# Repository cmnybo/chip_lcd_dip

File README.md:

# C.H.I.P. LCD Adapter & SPI Multiplexer

This DIP is compatible with the following touch screen LCD panels (resistive touch version only):

1. [4.3" 480x272](http://www.buydisplay.com/default/tft-4-3-inch-lcd-module-touchscreen-display-for-mp4-gps-480x272)
2. [5" 800x480](http://www.buydisplay.com/default/5-tft-lcd-display-module-wvga-800x480-high-resolution-for-mp4-gps)
3. [7" 800x480](http://www.buydisplay.com/default/7-tft-lcd-touch-screen-display-module-800x480-for-mp4-gps-tablet-pc)

## Features

* PWM controlled backlight driver
* 8 channel chip select multiplexer for SPI
* 34 pin gpio header that can be connected with old floppy drive cables
* Pin headers for the UART and power switch
* 5.5x2.5mm barrel jack to supply power (5V 2.5A)

The original design files for this board were created in [KiCAD](http://kicad-pcb.org/). <br/>
There are PDF copies of the schematic, PCB layout, and bill of materials in the "pdf" directory.<br/>
The "gerber" directory contains all of the files needed to have some boards made.<br/>
The device tree overlay, kernel patch, and EEPROM image are in the "source" directory.

## License
**This project is open source hardware.**

All files are licensed under a [Creative Commons Attribution-ShareAlike](https://creativecommons.org/licenses/by-sa/3.0) license.

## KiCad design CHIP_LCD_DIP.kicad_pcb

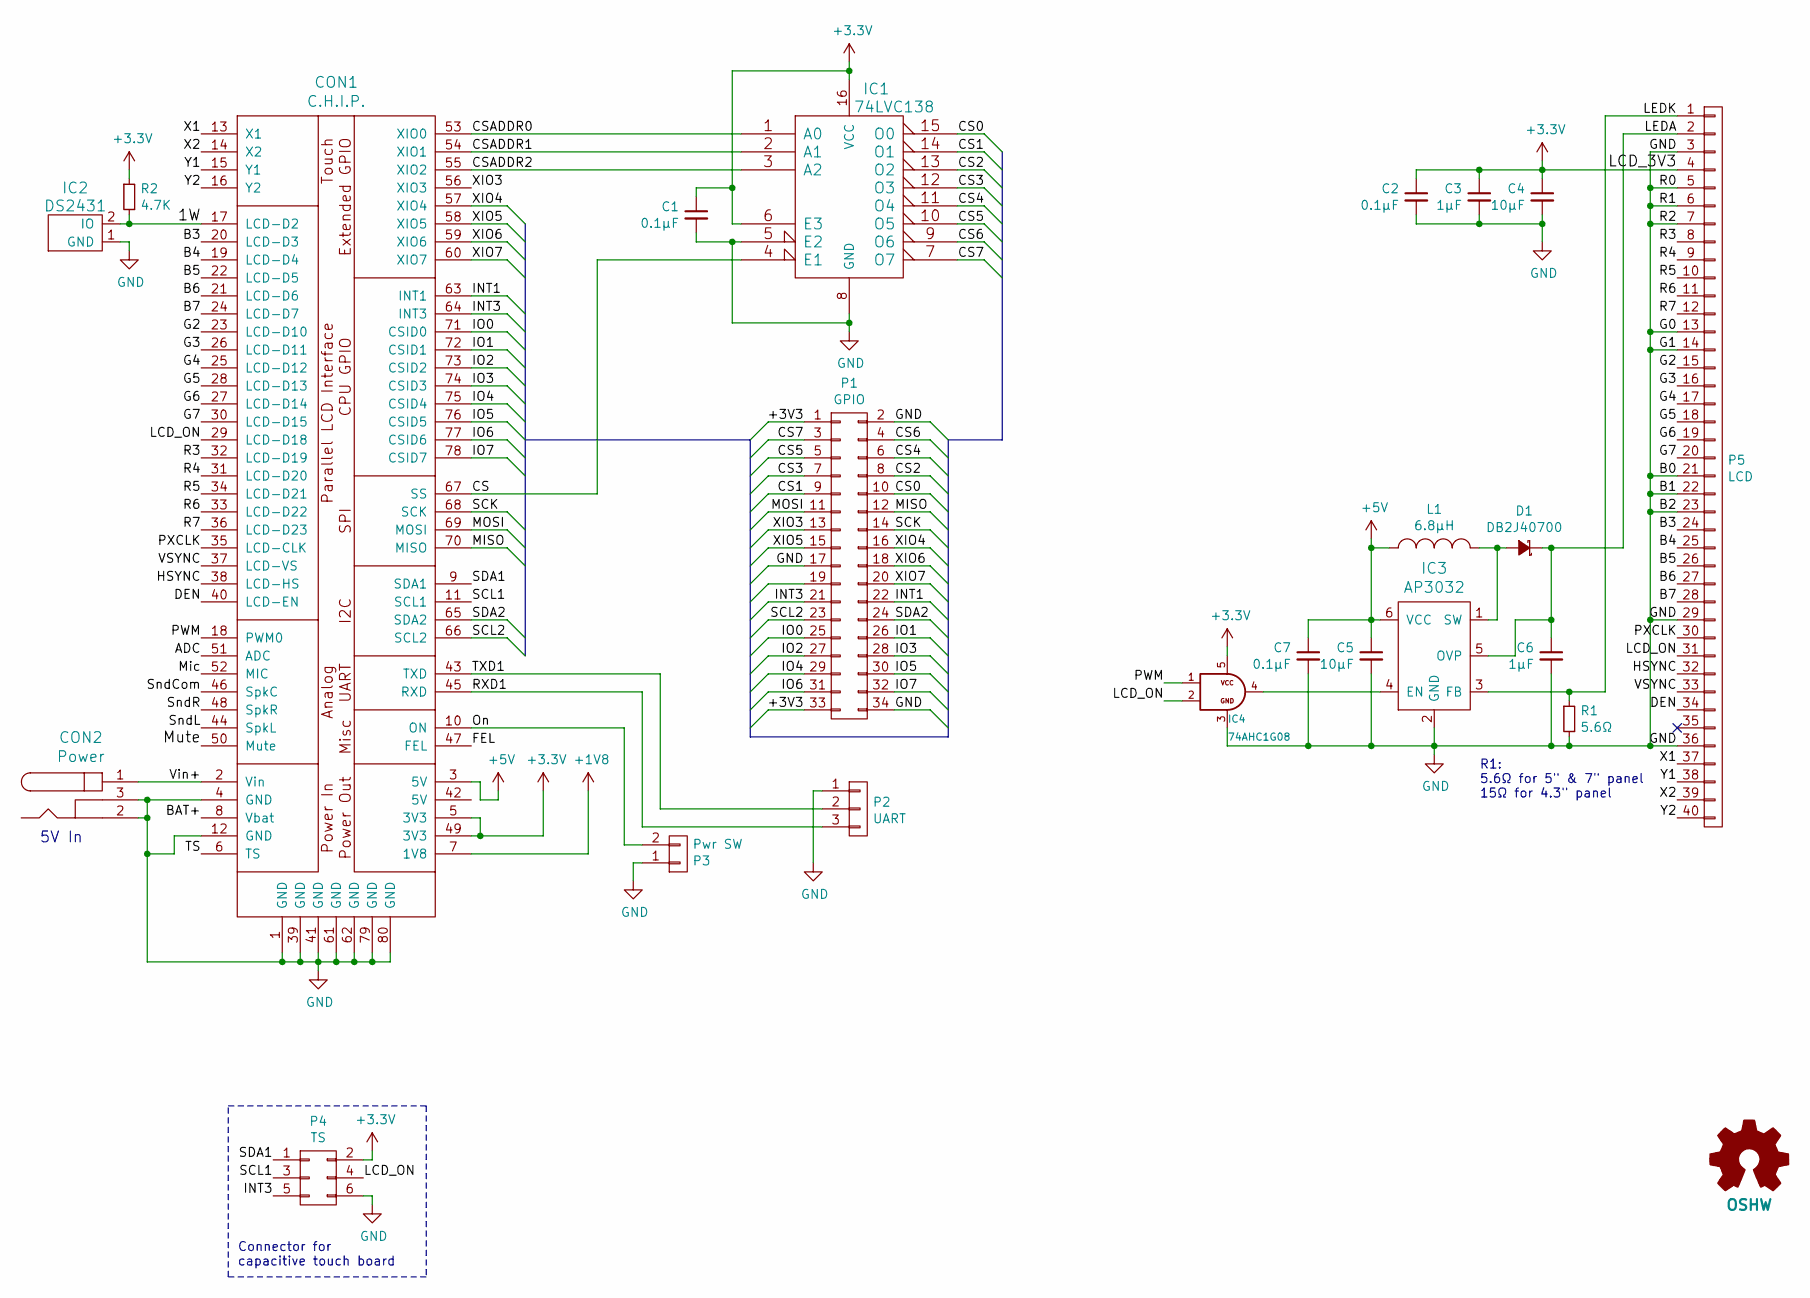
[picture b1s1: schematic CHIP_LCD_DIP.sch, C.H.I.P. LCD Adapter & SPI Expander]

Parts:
C1, C2, C7: 0.1µF; C_0603; Voltage 25V; Tolerance 10%; DigiKey 1276-1006-1-ND
C3: 1µF; C_0603; Voltage 16V; Tolerance 20%; DigiKey 1276-6524-1-ND
C4: 10µF; C_0805; Voltage 6.3V; Tolerance 10%; DigiKey 1276-6457-1-ND
C5: 10µF; C_0603; Voltage 6.3V; Tolerance 10%; DigiKey 490-12538-1-ND
C6: 1µF; C_0603; Voltage 50V; Tolerance 10%; DigiKey 1276-1860-1-ND
CON1: C.H.I.P.; CHIP_DIP
CON2: Power; BARREL_JACK; DigiKey CP-002B-ND
D1: DB2J40700; SOD-323; Voltage 40V; DigiKey DB2J40700LCT-ND
IC1: 74LVC138; SOIC-16_3.9x9.9mm_Pitch1.27mm; DigiKey 568-1577-5-ND
IC2: DS2431; TO-92_Inline_Narrow_Oval; DigiKey DS2431+-ND
IC3: AP3032; SOT-23-6; DigiKey AP3032KTR-G1DICT-ND
IC4: 74AHC1G08; SC-70-5; DigiKey 568-2501-1-ND
L1: 6.8µH; TDK_VLS-E-CA; Tolerance 20%; DigiKey 445-174144-1-ND
LOGO1: OSHW
P1: GPIO; vasch_strip_17x2; DigiKey ED10528-ND
P2: UART; Pin_Header_Straight_1x03; DigiKey 952-2245-ND
P3: Pwr SW; Pin_Header_Straight_1x02; DigiKey 952-2244-ND
P4: TS; 02x03_Header_0.05
P5: LCD; TE_40_PIN_LCD_Connector; DigiKey 609-1195-1-ND
R1: 5.6Ω; C_0603; Tolerance 5%; Voltage 75V; DigiKey 311-5.6GRCT-ND
R2: 4.7K; C_0603; Tolerance 5%; Voltage 75V; DigiKey 311-4.7KGRCT-ND

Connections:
+1V8: CON1.7 (1V8)
+5V: C5.1, C7.1, CON1.3 (5V), IC3.6 (VCC), L1.1
/1W: CON1.17 (LCD-D2), IC2.2 (IO), R2.2
/ADC: CON1.51 (ADC)
/B3: CON1.20 (LCD-D3), P5.24
/B4: CON1.19 (LCD-D4), P5.25
/B5: CON1.22 (LCD-D5), P5.26
/B6: CON1.21 (LCD-D6), P5.27
/B7: CON1.24 (LCD-D7), P5.28
/BAT+: CON1.8 (Vbat)
/CS: CON1.67 (SS), IC1.4 (E1)
/CS0: IC1.15 (O0), P1.10
/CS1: IC1.14 (O1), P1.9
/CS2: IC1.13 (O2), P1.8
/CS3: IC1.12 (O3), P1.7
/CS4: IC1.11 (O4), P1.6
/CS5: IC1.10 (O5), P1.5
/CS6: IC1.9 (O6), P1.4
/CS7: IC1.7 (O7), P1.3
/CSADDR0: CON1.53 (XIO0), IC1.1 (A0)
/CSADDR1: CON1.54 (XIO1), IC1.2 (A1)
/CSADDR2: CON1.55 (XIO2), IC1.3 (A2)
/DEN: CON1.40 (LCD-EN), P5.34
/FEL: CON1.47 (FEL)
/G2: CON1.23 (LCD-D10), P5.15
/G3: CON1.26 (LCD-D11), P5.16
/G4: CON1.25 (LCD-D12), P5.17
/G5: CON1.28 (LCD-D13), P5.18
/G6: CON1.27 (LCD-D14), P5.19
/G7: CON1.30 (LCD-D15), P5.20
/HSYNC: CON1.38 (LCD-HS), P5.32
/INT1: CON1.63 (INT1), P1.22
/INT3: CON1.64 (INT3), P1.21, P4.5
/IO0: CON1.71 (CSID0), P1.25
/IO1: CON1.72 (CSID1), P1.26
/IO2: CON1.73 (CSID2), P1.27
/IO3: CON1.74 (CSID3), P1.28
/IO4: CON1.75 (CSID4), P1.29
/IO5: CON1.76 (CSID5), P1.30
/IO6: CON1.77 (CSID6), P1.31
/IO7: CON1.78 (CSID7), P1.32
/LCD_ON: CON1.29 (LCD-D18), IC4.2, P4.4, P5.31
/LEDA: C6.1, D1.1 (K), IC3.5 (OVP), P5.2
/LEDK: IC3.3 (FB), P5.1, R1.1
/MISO: CON1.70 (MISO), P1.12
/MOSI: CON1.69 (MOSI), P1.11
/Mic: CON1.52 (MIC)
/Mute: CON1.50 (Mute)
/On: CON1.10 (ON), P3.2
/PWM: CON1.18 (PWM0), IC4.1
/PXCLK: CON1.35 (LCD-CLK), P5.30
/R3: CON1.32 (LCD-D19), P5.8
/R4: CON1.31 (LCD-D20), P5.9
/R5: CON1.34 (LCD-D21), P5.10
/R6: CON1.33 (LCD-D22), P5.11
/R7: CON1.36 (LCD-D23), P5.12
/RXD1: CON1.45 (RXD), P2.3
/SCK: CON1.68 (SCK), P1.14
/SCL1: CON1.11 (SCL1), P4.3
/SCL2: CON1.66 (SCL2), P1.23
/SDA1: CON1.9 (SDA1), P4.1
/SDA2: CON1.65 (SDA2), P1.24
/SndCom: CON1.46 (SpkC)
/SndL: CON1.44 (SpkL)
/SndR: CON1.48 (SpkR)
/TS: CON1.6 (TS)
/TXD1: CON1.43 (TXD), P2.2
/VSYNC: CON1.37 (LCD-VS), P5.33
/Vin+: CON1.2 (Vin), CON2.1
/X1: CON1.13 (X1), P5.37
/X2: CON1.14 (X2), P5.39
/XIO3: CON1.56 (XIO3), P1.13
/XIO4: CON1.57 (XIO4), P1.16
/XIO5: CON1.58 (XIO5), P1.15
/XIO6: CON1.59 (XIO6), P1.18
/XIO7: CON1.60 (XIO7), P1.20
/Y1: CON1.15 (Y1), P5.38
/Y2: CON1.16 (Y2), P5.40
GND: C1.2, C2.2, C3.2, C4.2, C5.2, C6.2, C7.2, CON1.1 (GND), CON1.4 (GND), CON1.12 (GND), CON1.39 (GND), CON1.41 (GND), CON1.61 (GND), CON1.62 (GND), CON1.79 (GND), CON1.80 (GND), CON2.2, CON2.3, IC1.5 (E2), IC1.8 (GND), IC2.1 (GND), IC3.2 (GND), IC4.3, P1.2, P1.17, P1.34, P2.1, P3.1, P4.6, P5.3, P5.5, P5.6, P5.7, P5.13, P5.14, P5.21, P5.22, P5.23, P5.29, P5.36, R1.2
unnamed: D1.2 (A), IC3.1 (SW), L1.2
unnamed: IC3.4 (EN), IC4.4

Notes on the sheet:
R1: 5.6Ω for 5" & 7" panel 15Ω for 4.3" panel
5V In
Connector for capacitive touch board

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
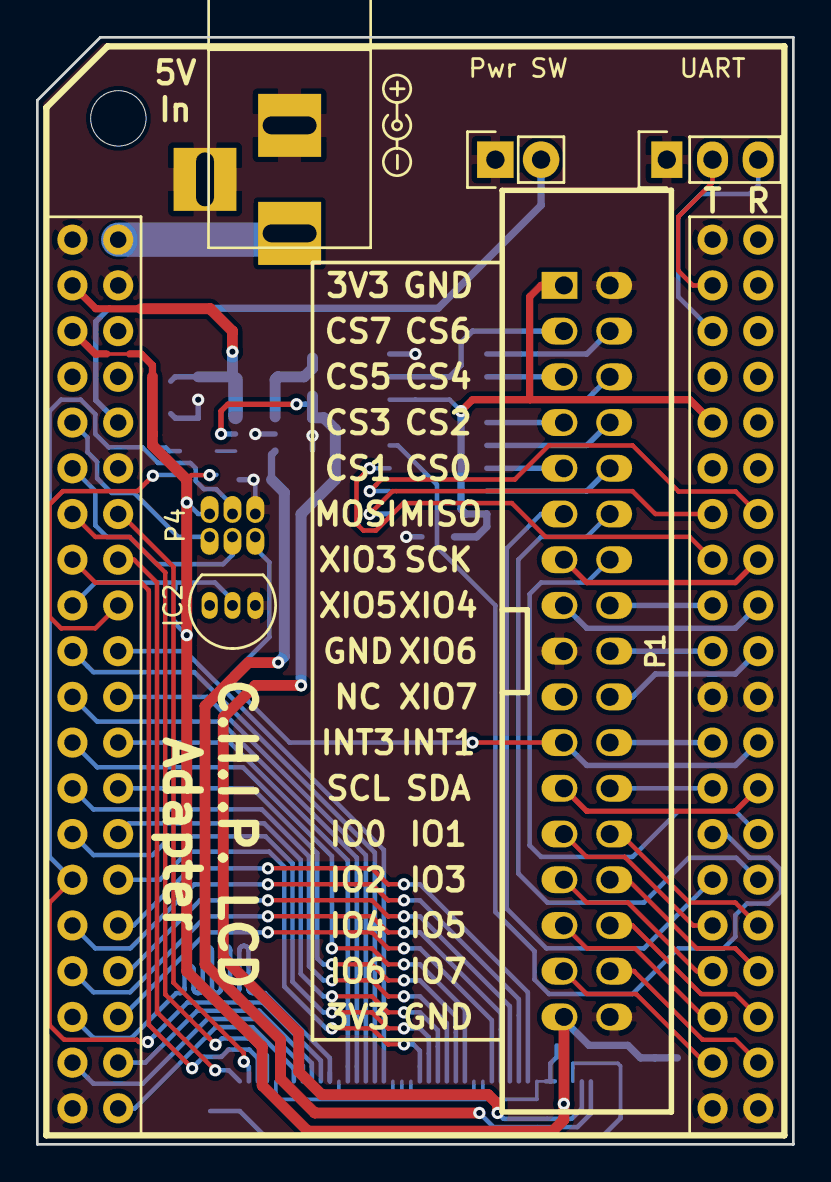
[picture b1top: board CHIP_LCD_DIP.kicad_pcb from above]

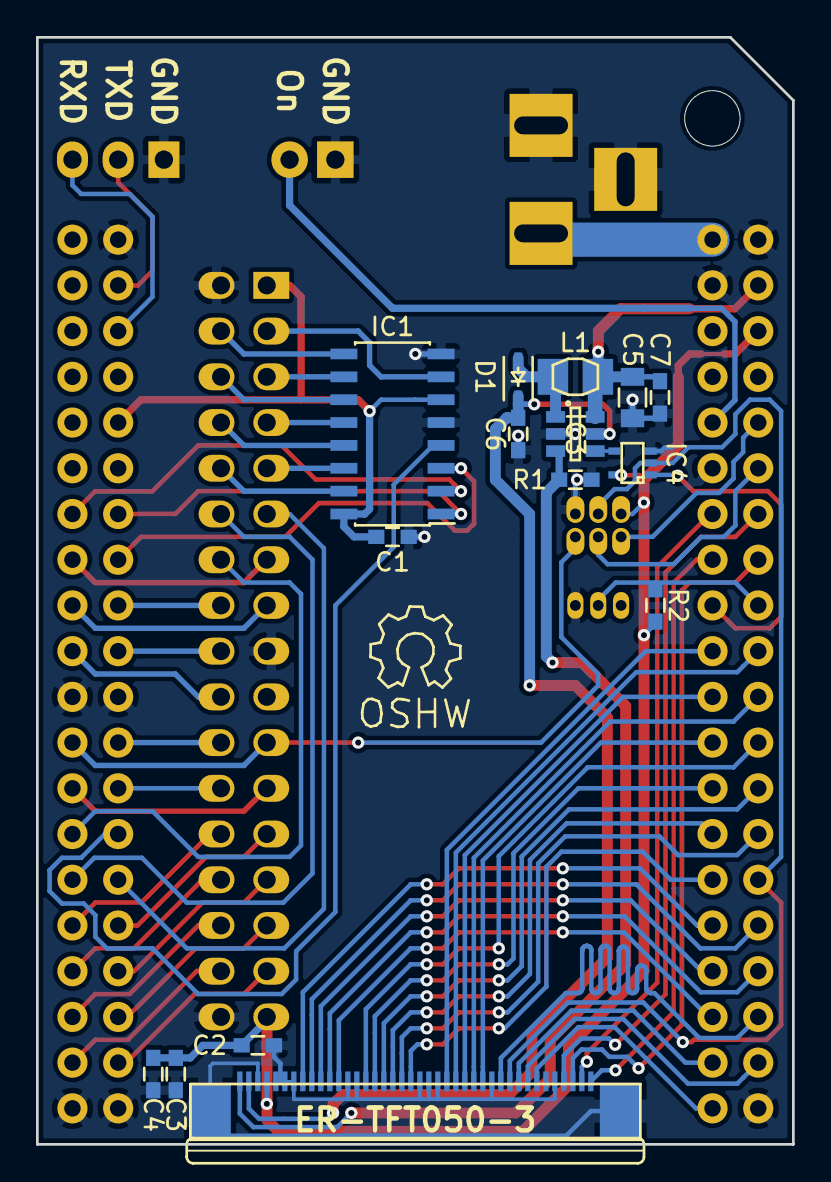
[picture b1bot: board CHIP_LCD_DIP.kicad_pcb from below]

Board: 2 copper layers, 42.0 x 61.5 mm, 22 parts (15 on the bottom side), 72 nets.

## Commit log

2016-09-01 Added gerber files
2016-09-02 Added connector to go to optional capacitive touch board.
2016-10-15 Updated files. Added source code. Added pdf copies of design files.
2016-10-15 Updated device tree overlay
